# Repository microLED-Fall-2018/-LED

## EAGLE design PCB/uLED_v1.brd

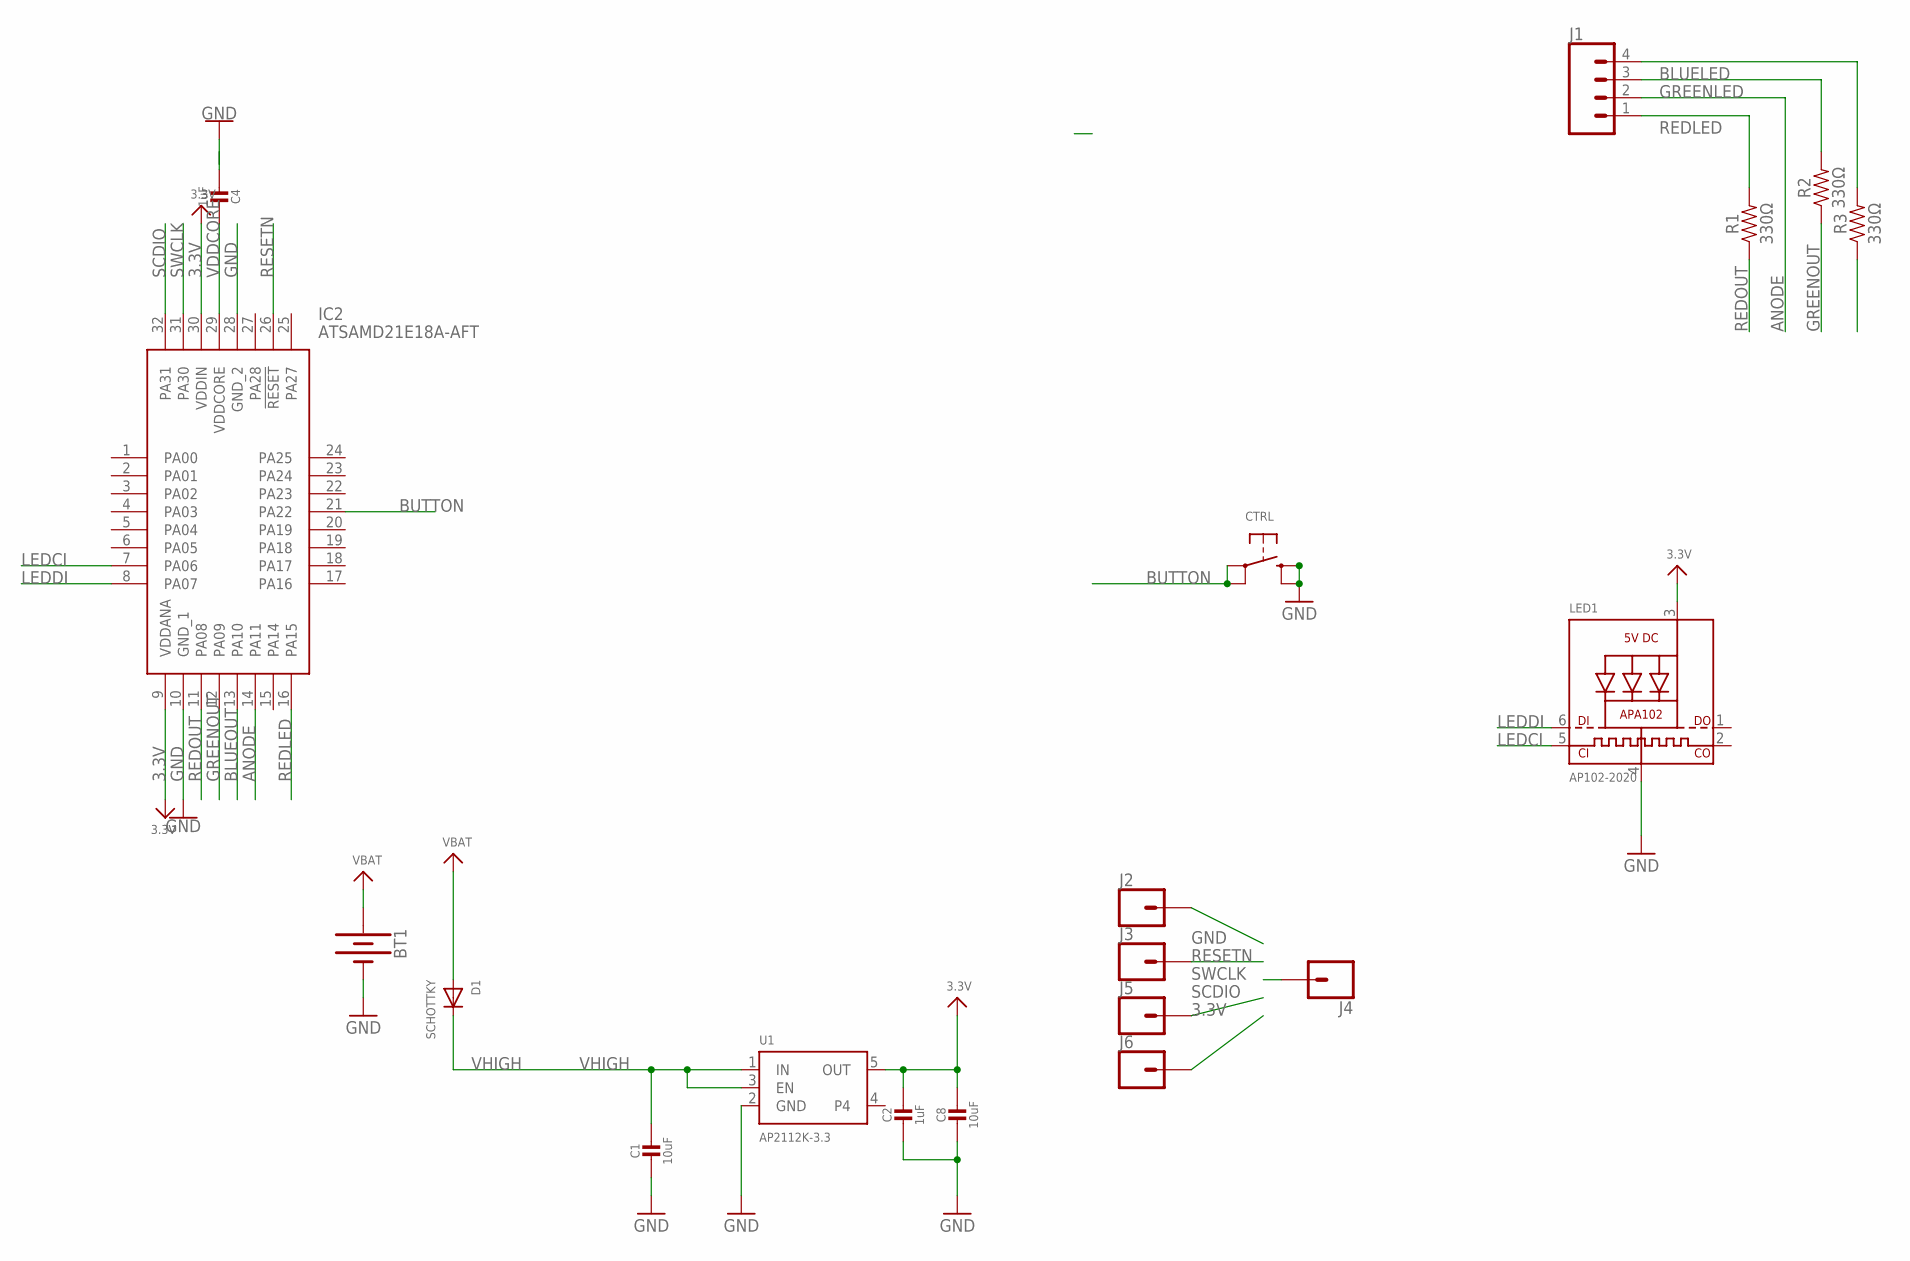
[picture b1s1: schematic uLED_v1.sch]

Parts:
BT1: BATTERY-12MM_SMD; BATTCON_12MM
C1, C8: 10uF; 0805-NO
C2, C4: 1uF; 0603-NO
CTRL: SWITCH_TACT_SMT4.6X2.8; BTN_KMR2_4.6X2.8
D1: SCHOTTKY; SOD-123FL
IC2: ATSAMD21E18A-AFT; QFP80P900X900X120-32N
J1: CONN_04; 1X04
J2, J3, J4, J5, J6: CONN_01; 1X01
LED1: AP102-2020; APA102_2020
R1, R2, R3: 330Ω; 0603
U1: AP2112K-3.3; SOT23-5

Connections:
3.3V: C2.1, C8.1, IC2.9 (VDDANA), IC2.30 (VDDIN), J6.1, LED1.3 (VDD), U1.5 (OUT)
ANODE: IC2.14 (PA11), J1.2
BLUELED: J1.4, R3.2
BLUEOUT: IC2.13 (PA10), R3.1
BUTTON: CTRL.A, CTRL.A' (P1), IC2.21 (PA22)
GND: BT1.GND (-), C1.2, C2.2, C4.2, C8.2, CTRL.B (S), CTRL.B' (S1), IC2.10 (GND_1), IC2.28 (GND_2), J2.1, LED1.4 (GND), U1.2 (GND)
GREENLED: J1.3, R2.2
GREENOUT: IC2.12 (PA09), R2.1
LEDCI: IC2.7 (PA06), LED1.5 (CKI)
LEDDI: IC2.8 (PA07), LED1.6 (DI)
REDLED: IC2.16 (PA15), J1.1, R1.2
REDOUT: IC2.11 (PA08), R1.1
RESETN: IC2.26 (!RESET), J3.1
SCDIO: IC2.32 (PA31), J5.1
SWCLK: IC2.31 (PA30), J4.1
VBAT: BT1.PWR@1 (+), D1.A
VDDCORE: C4.1, IC2.29 (VDDCORE)
VHIGH: C1.1, D1.C, U1.1 (IN), U1.3 (EN)

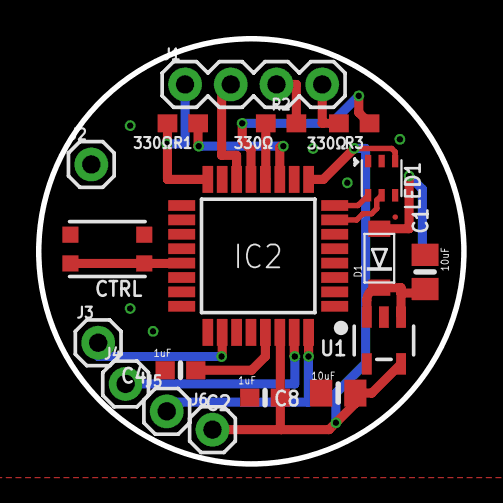
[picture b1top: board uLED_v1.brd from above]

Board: 2 copper layers, 23.6 x 23.6 mm, 19 parts (1 on the bottom side), 18 nets.

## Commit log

2018-07-28 working exporting json
2018-09-04 Forms to arduino communication
2018-09-04 added color selection preview to color guru
2018-09-07 Adding basic blinky
2018-09-09 update to basic blinky
2018-09-18 new ui
2018-10-04 Basic Blinky (all wrong)
2018-10-05 Adding rough VLC stuff (but it works!!!)
2018-10-19 start eagle file
2018-10-20 update ui
2018-10-20 working adc vlc
2018-10-21 working vlc between sender and receiver on same clock
2018-10-21 mend
2018-10-22 updated basic blinky
2018-10-22 updating basic blinky
2018-10-22 Working Fades and Ramps
2018-10-29 save from my battery
2018-10-29 Updated PCB
2018-10-30 PBG in progress
2018-10-31 Updating board again
2018-11-01 yet another pcb
2018-11-01 PCB version 1 final
2018-11-05 adding UART4Debugging
2018-11-07 anotherDotstar, dotStar, CdC, and button
2018-11-24 Saturday Morning Commit
2018-11-28 Adding new PCB 16mm
2018-11-28 Adding bpm control and sequence change to e18a
2018-12-02 add current code for 2 clock vlc
2018-12-02 Adding ADC to anotherDotstar
2018-12-03 2 clock vlc done
2018-12-04 cleaned up frontend and fixed Serial Output
2018-12-04 added assets to project path
2018-12-04 fixed gitnore and cleaned up project
2018-12-04 refactor, reorganize, and small fix for frontend
2018-12-06 start bitmap gen for sequence and made VLC data frame detection more accurate
2018-12-07 Stuff
2018-12-07 frontend fixes and send string over vlc

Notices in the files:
parts and their libraries:
microbuilder: This work is placed in the public domain, and may be freely used for commercial and non-commercial work with the following conditions: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
SparkFun-Resistors: Licensing: Creative Commons ShareAlike 4.0 International - https://creativecommons.org/licenses/by-sa/4.0
